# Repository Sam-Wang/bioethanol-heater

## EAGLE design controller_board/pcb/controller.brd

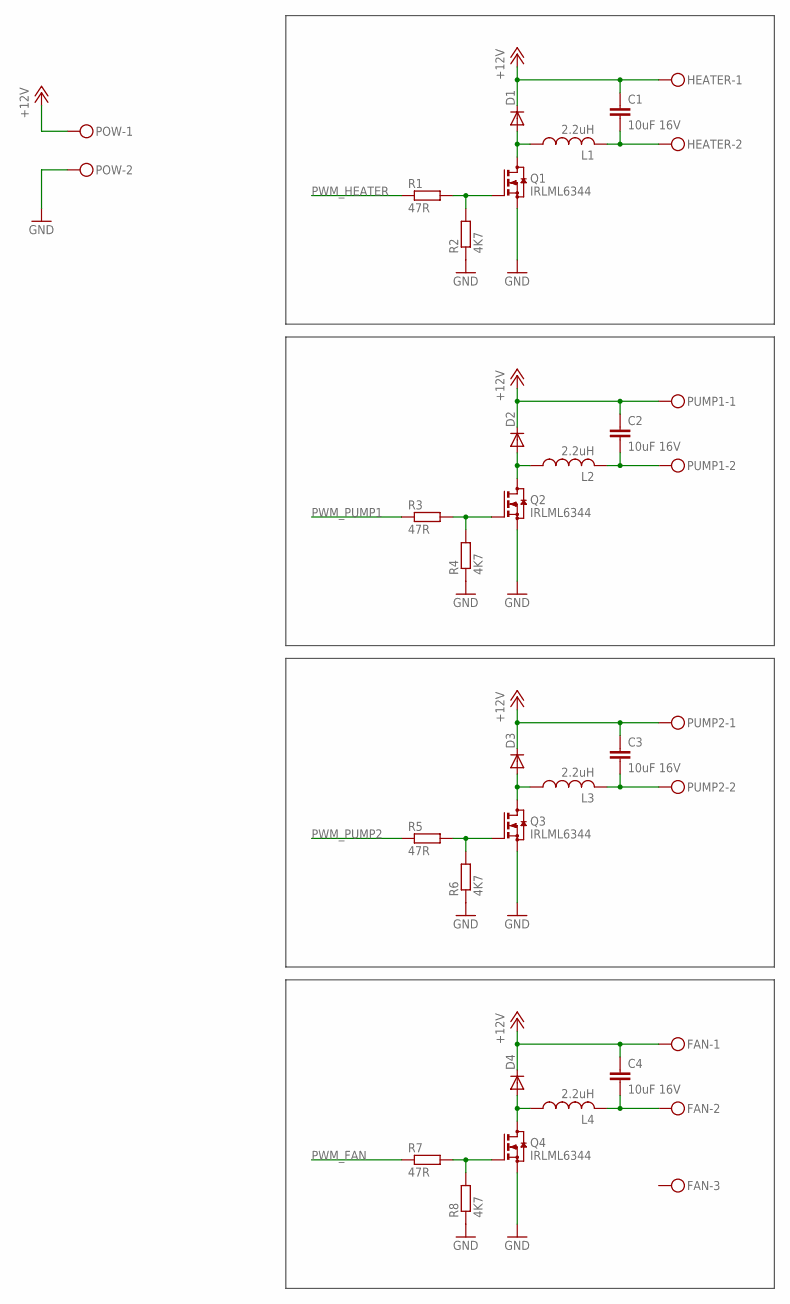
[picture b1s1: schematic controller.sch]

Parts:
C1, C2, C3, C4: 10uF 16V; C1206
D1, D2, D3, D4: DIODE-MINIMELF; MINIMELF
FAN: PTSM-0.5/3-2.5-HTHR; PTSM-0.5/3-2.5-H-THR
HEATER: PTSM-0.5/2-2.5-HTHR; PTSM-0.5/2-2.5-H-THR
L1, L2, L3, L4: 2.2uH; L3225M
POW: PTSM-0.5/2-2.5-HTHR; PTSM-0.5/2-2.5-H-THR
PUMP1, PUMP2: PTSM-0.5/2-2.5-HTHR; PTSM-0.5/2-2.5-H-THR
Q1, Q2, Q3, Q4: IRLML6344; SOT23
R1, R3, R5, R7: 47R; R0603
R2, R4, R6, R8: 4K7; R0603

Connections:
+12V: C1.1, C2.1, C3.1, C4.1, D1.C, D2.C, D3.C, D4.C, FAN.1A, FAN.1B, HEATER.1A, HEATER.1B, POW.1A, POW.1B, PUMP1.1A, PUMP1.1B, PUMP2.1A, PUMP2.1B
GND: POW.2A, POW.2B, Q1.2 (S), Q2.2 (S), Q3.2 (S), Q4.2 (S), R2.1, R4.1, R6.1, R8.1
unnamed: D2.A, L2.1, Q2.3 (D)
unnamed: D1.A, L1.1, Q1.3 (D)
unnamed: C1.2, HEATER.2A, HEATER.2B, L1.2
unnamed: Q1.1 (G), R1.2, R2.2
unnamed: C2.2, L2.2, PUMP1.2A, PUMP1.2B
unnamed: Q2.1 (G), R3.2, R4.2
unnamed: D3.A, L3.1, Q3.3 (D)
unnamed: C3.2, L3.2, PUMP2.2A, PUMP2.2B
unnamed: Q3.1 (G), R5.2, R6.2
unnamed: D4.A, L4.1, Q4.3 (D)
unnamed: C4.2, FAN.2A, FAN.2B, L4.2
unnamed: Q4.1 (G), R7.2, R8.2
PWM_FAN: R7.1
PWM_HEATER: R1.1
PWM_PUMP1: R3.1
PWM_PUMP2: R5.1

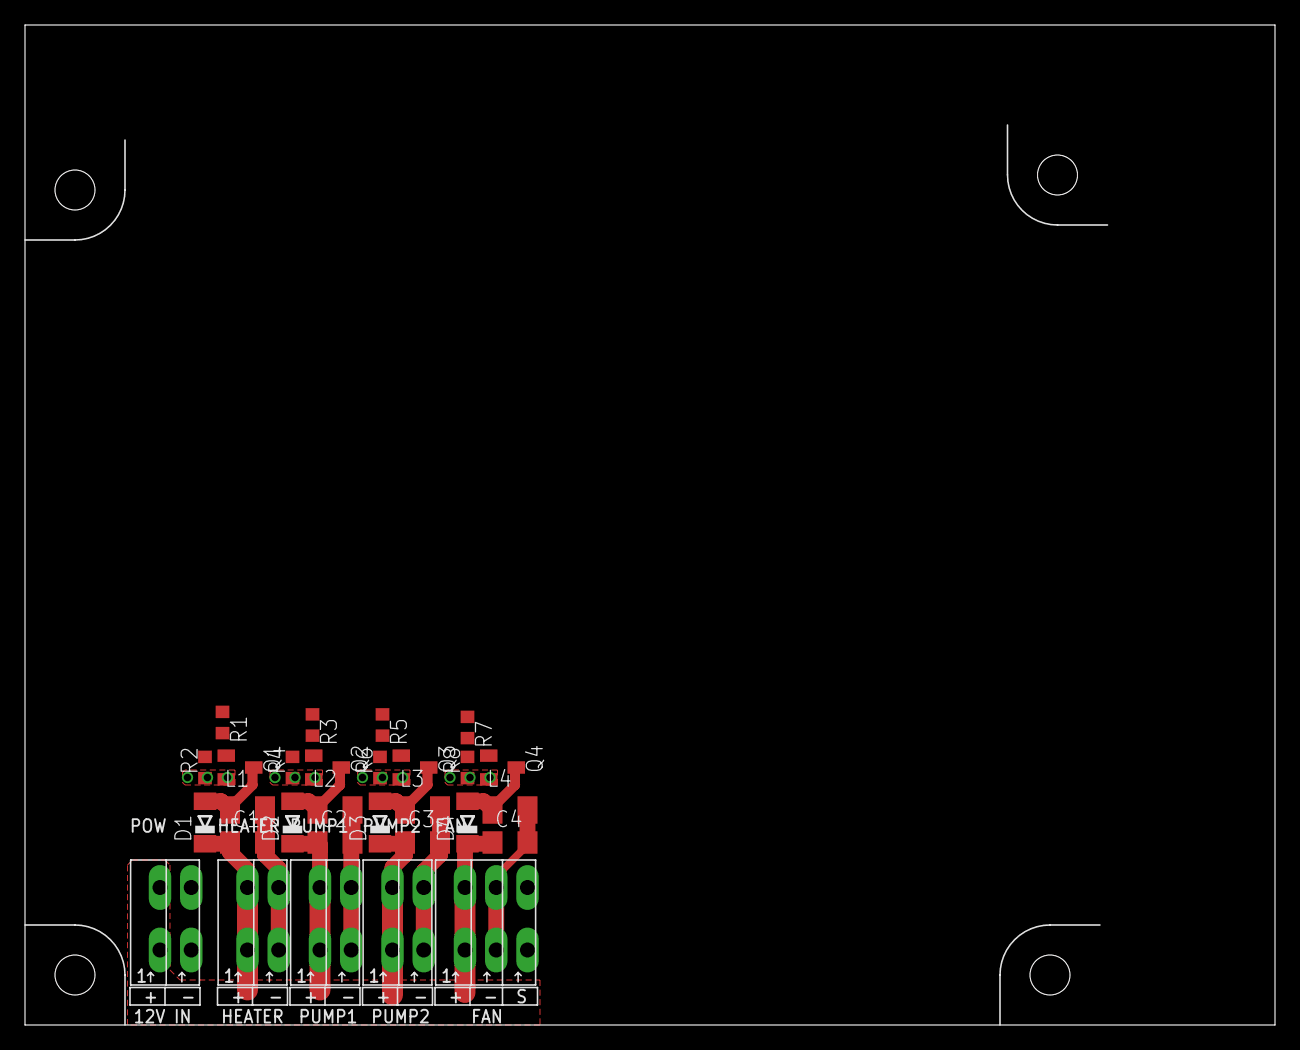
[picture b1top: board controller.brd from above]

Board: 2 copper layers, 100.0 x 80.0 mm, 29 parts (0 on the bottom side), 14 nets.

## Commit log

2016-01-07 Add basic heater drawing
2016-01-07 Add high power PWM outputs + layout
